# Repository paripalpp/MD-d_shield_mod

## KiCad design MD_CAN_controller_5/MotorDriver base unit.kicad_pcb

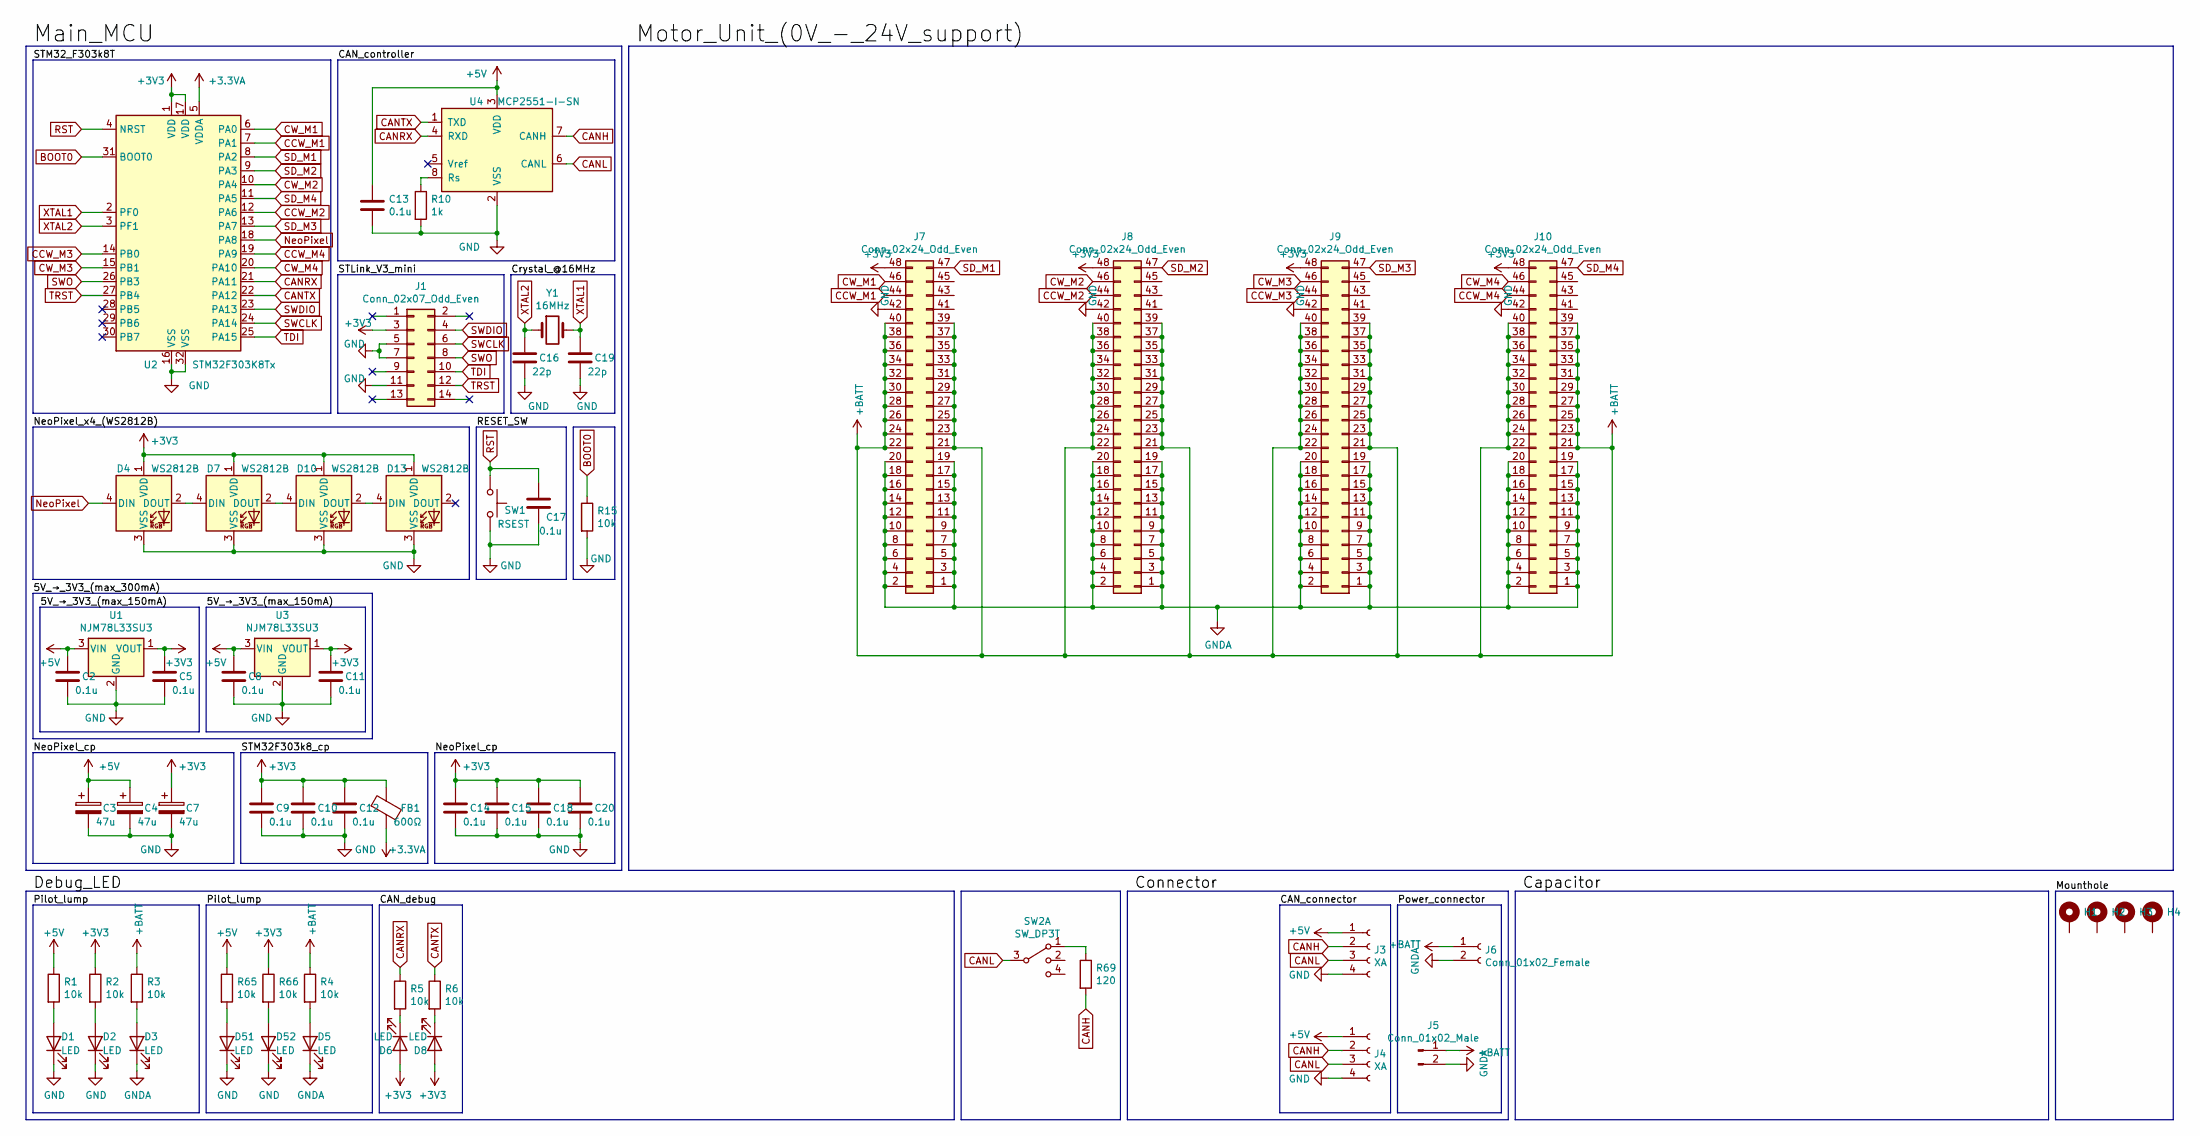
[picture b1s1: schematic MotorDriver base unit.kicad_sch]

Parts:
C2, C5, C8, C9, C10, C11, C12, C13, C14, C15, C17, C18, C20: 0.1u; C_0603_1608Metric
C3, C4, C7: 47u; CP_Elec_6.3x5.2
C16, C19: 22p; C_0603_1608Metric
D1, D2, D3, D5, D6, D8, D51, D52: LED; LED_0603_1608Metric
D4, D7, D10, D13: WS2812B; LED_WS2812B_PLCC4_5.0x5.0mm_P3.2mm
FB1: 600Ω; L_0603_1608Metric
H1, H2, H3, H4: MountingHole_Pad; MountingHole_3.2mm_M3_Pad_Via
J1: Conn_02x07_Odd_Even; PinHeader_2x07_P1.27mm_Vertical
J3, J4: XA; S04B-XASK-1
J5: Conn_01x02_Male; T_connecter_male_horizontal
J6: Conn_01x02_Female; T_connecter_female_horizontal
J7, J8, J9, J10: Conn_02x24_Odd_Even; PinSocket_2x24_P2.54mm_Vertical
R1, R2, R3, R4, R5, R6, R15, R65, R66: 10k; R_0603_1608Metric
R10: 1k; R_0603_1608Metric
R69: 120; R_0603_1608Metric
SW1: RSEST; SW_PUSH_6mm_H4.3mm
SW2: SW_DP3T; CL-SB-13A-01
U1, U3: NJM78L33SU3; SOT-89-3
U2: STM32F303K8Tx; LQFP-32_7x7mm_P0.8mm
U4: MCP2551-I-SN; SOIC-8_3.9x4.9mm_P1.27mm
Y1: 16MHz; Crystal_SMD_HC49-SD

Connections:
+3.3VA: FB1.2, U2.5 (VDDA)
+3V3: C5.1, C7.1, C9.1, C10.1, C11.1, C12.1, C14.1, C15.1, C18.1, C20.1, D4.1 (VDD), D6.2 (A), D7.1 (VDD), D8.2 (A), D10.1 (VDD), D13.1 (VDD), FB1.1, J1.3, J7.48, J8.48, J9.48, J10.48, R2.1, R66.1, U1.1 (VOUT), U2.1 (VDD), U2.17 (VDD), U3.1 (VOUT)
+5V: C2.1, C3.1, C4.1, C8.1, C13.1, J3.1, J4.1, R1.1, R65.1, U1.3 (VIN), U3.3 (VIN), U4.3 (VDD)
+BATT: J5.1, J6.1, J7.21, J7.22, J7.23, J7.24, J7.25, J7.26, J7.27, J7.28, J7.29, J7.30, J7.31, J7.32, J7.33, J7.34, J7.35, J7.36, J7.37, J7.38, J7.39, J7.40, J8.21, J8.22, J8.23, J8.24, J8.25, J8.26, J8.27, J8.28, J8.29, J8.30, J8.31, J8.32, J8.33, J8.34, J8.35, J8.36, J8.37, J8.38, J8.39, J8.40, J9.21, J9.22, J9.23, J9.24, J9.25, J9.26, J9.27, J9.28, J9.29, J9.30, J9.31, J9.32, J9.33, J9.34, J9.35, J9.36, J9.37, J9.38, J9.39, J9.40, J10.21, J10.22, J10.23, J10.24, J10.25, J10.26, J10.27, J10.28, J10.29, J10.30, J10.31, J10.32, J10.33, J10.34, J10.35, J10.36, J10.37, J10.38, J10.39, J10.40, R3.1, R4.1
BOOT0: R15.1, U2.31 (BOOT0)
CANH: J3.2, J4.2, R69.2, U4.7 (CANH)
CANL: J3.3, J4.3, SW2.3, U4.6 (CANL)
CANRX: R5.1, U2.21 (PA11), U4.4 (RXD)
CANTX: R6.1, U2.22 (PA12), U4.1 (TXD)
CCW_M1: J7.44, U2.7 (PA1)
CCW_M2: J8.44, U2.12 (PA6)
CCW_M3: J9.44, U2.14 (PB0)
CCW_M4: J10.44, U2.19 (PA9)
CW_M1: J7.46, U2.6 (PA0)
CW_M2: J8.46, U2.10 (PA4)
CW_M3: J9.46, U2.15 (PB1)
CW_M4: J10.46, U2.20 (PA10)
GND: C2.2, C3.2, C4.2, C5.2, C7.2, C8.2, C9.2, C10.2, C11.2, C12.2, C13.2, C14.2, C15.2, C16.2, C17.2, C18.2, C19.2, C20.2, D1.1 (K), D2.1 (K), D4.3 (VSS), D7.3 (VSS), D10.3 (VSS), D13.3 (VSS), D51.1 (K), D52.1 (K), J1.5, J1.7, J1.11, J3.4, J4.4, J7.42, J8.42, J9.42, J10.42, R10.2, R15.2, SW1.2, U1.2 (GND), U2.16 (VSS), U2.32 (VSS), U3.2 (GND), U4.2 (VSS)
GNDA: D3.1 (K), D5.1 (K), J5.2, J6.2, J7.1, J7.2, J7.3, J7.4, J7.5, J7.6, J7.7, J7.8, J7.9, J7.10, J7.11, J7.12, J7.13, J7.14, J7.15, J7.16, J7.17, J7.18, J7.19, J7.20, J8.1, J8.2, J8.3, J8.4, J8.5, J8.6, J8.7, J8.8, J8.9, J8.10, J8.11, J8.12, J8.13, J8.14, J8.15, J8.16, J8.17, J8.18, J8.19, J8.20, J9.1, J9.2, J9.3, J9.4, J9.5, J9.6, J9.7, J9.8, J9.9, J9.10, J9.11, J9.12, J9.13, J9.14, J9.15, J9.16, J9.17, J9.18, J9.19, J9.20, J10.1, J10.2, J10.3, J10.4, J10.5, J10.6, J10.7, J10.8, J10.9, J10.10, J10.11, J10.12, J10.13, J10.14, J10.15, J10.16, J10.17, J10.18, J10.19, J10.20
NeoPixel: D4.4 (DIN), U2.18 (PA8)
unnamed: D1.2 (A), R1.2
unnamed: D2.2 (A), R2.2
unnamed: D3.2 (A), R3.2
unnamed: D4.2 (DOUT), D7.4 (DIN)
unnamed: D5.2 (A), R4.2
unnamed: D6.1 (K), R5.2
unnamed: D8.1 (K), R6.2
unnamed: D10.2 (DOUT), D13.4 (DIN)
unnamed: D7.2 (DOUT), D10.4 (DIN)
unnamed: D51.2 (A), R65.2
unnamed: D52.2 (A), R66.2
unnamed: R10.1, U4.8 (Rs)
unnamed: R69.1, SW2.1
RST: C17.1, SW1.1, U2.4 (NRST)
SD_M1: J7.47, U2.8 (PA2)
SD_M2: J8.47, U2.9 (PA3)
SD_M3: J9.47, U2.13 (PA7)
SD_M4: J10.47, U2.11 (PA5)
SWCLK: J1.6, U2.24 (PA14)
SWDIO: J1.4, U2.23 (PA13)
SWO: J1.8, U2.26 (PB3)
TDI: J1.10, U2.25 (PA15)
TRST: J1.12, U2.27 (PB4)
XTAL1: C19.1, U2.2 (PF0), Y1.2
XTAL2: C16.1, U2.3 (PF1), Y1.1

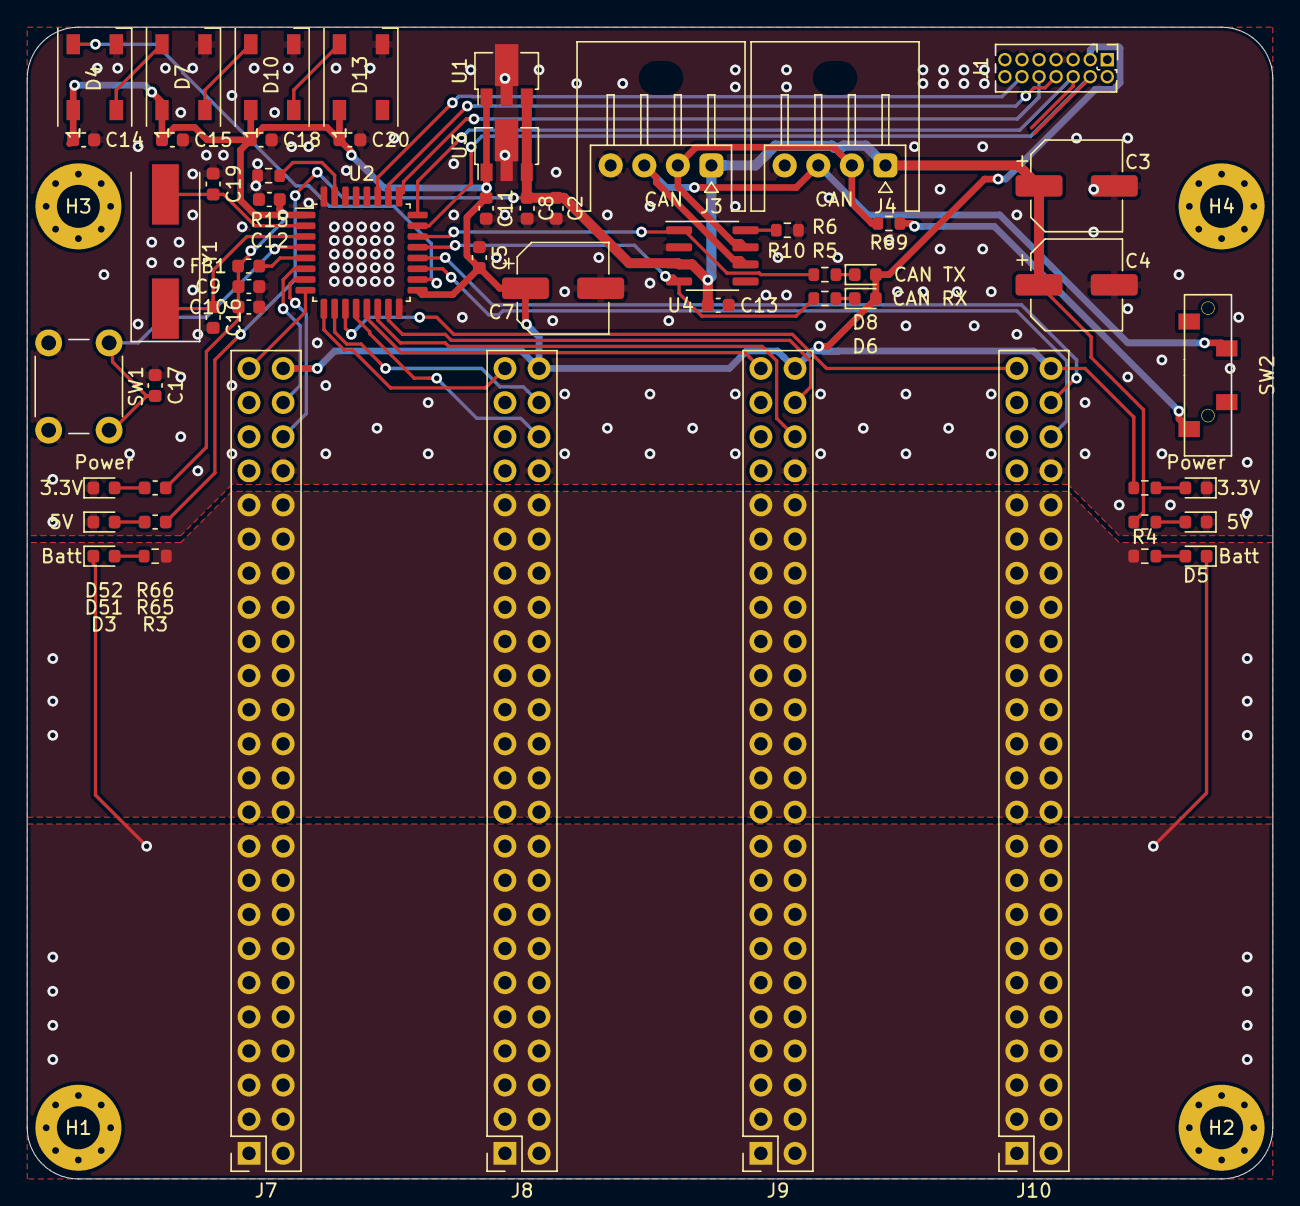
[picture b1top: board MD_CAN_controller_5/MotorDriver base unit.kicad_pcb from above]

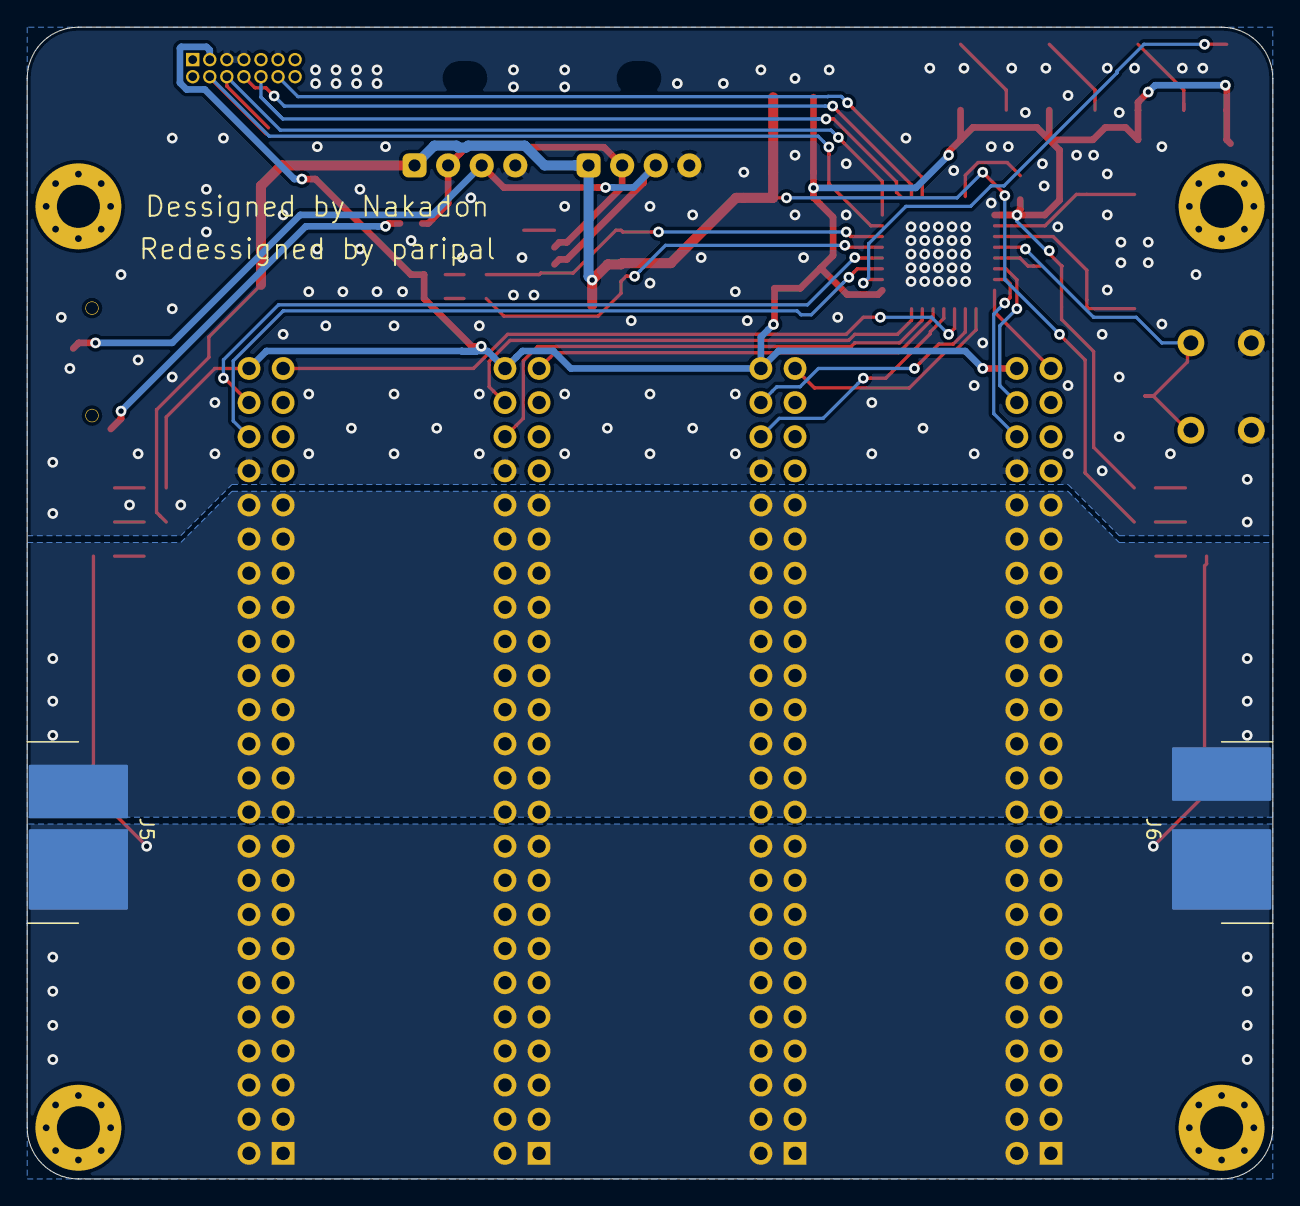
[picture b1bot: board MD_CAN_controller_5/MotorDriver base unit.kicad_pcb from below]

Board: 2 copper layers, 92.7 x 85.7 mm, 62 parts (2 on the bottom side), 45 nets.

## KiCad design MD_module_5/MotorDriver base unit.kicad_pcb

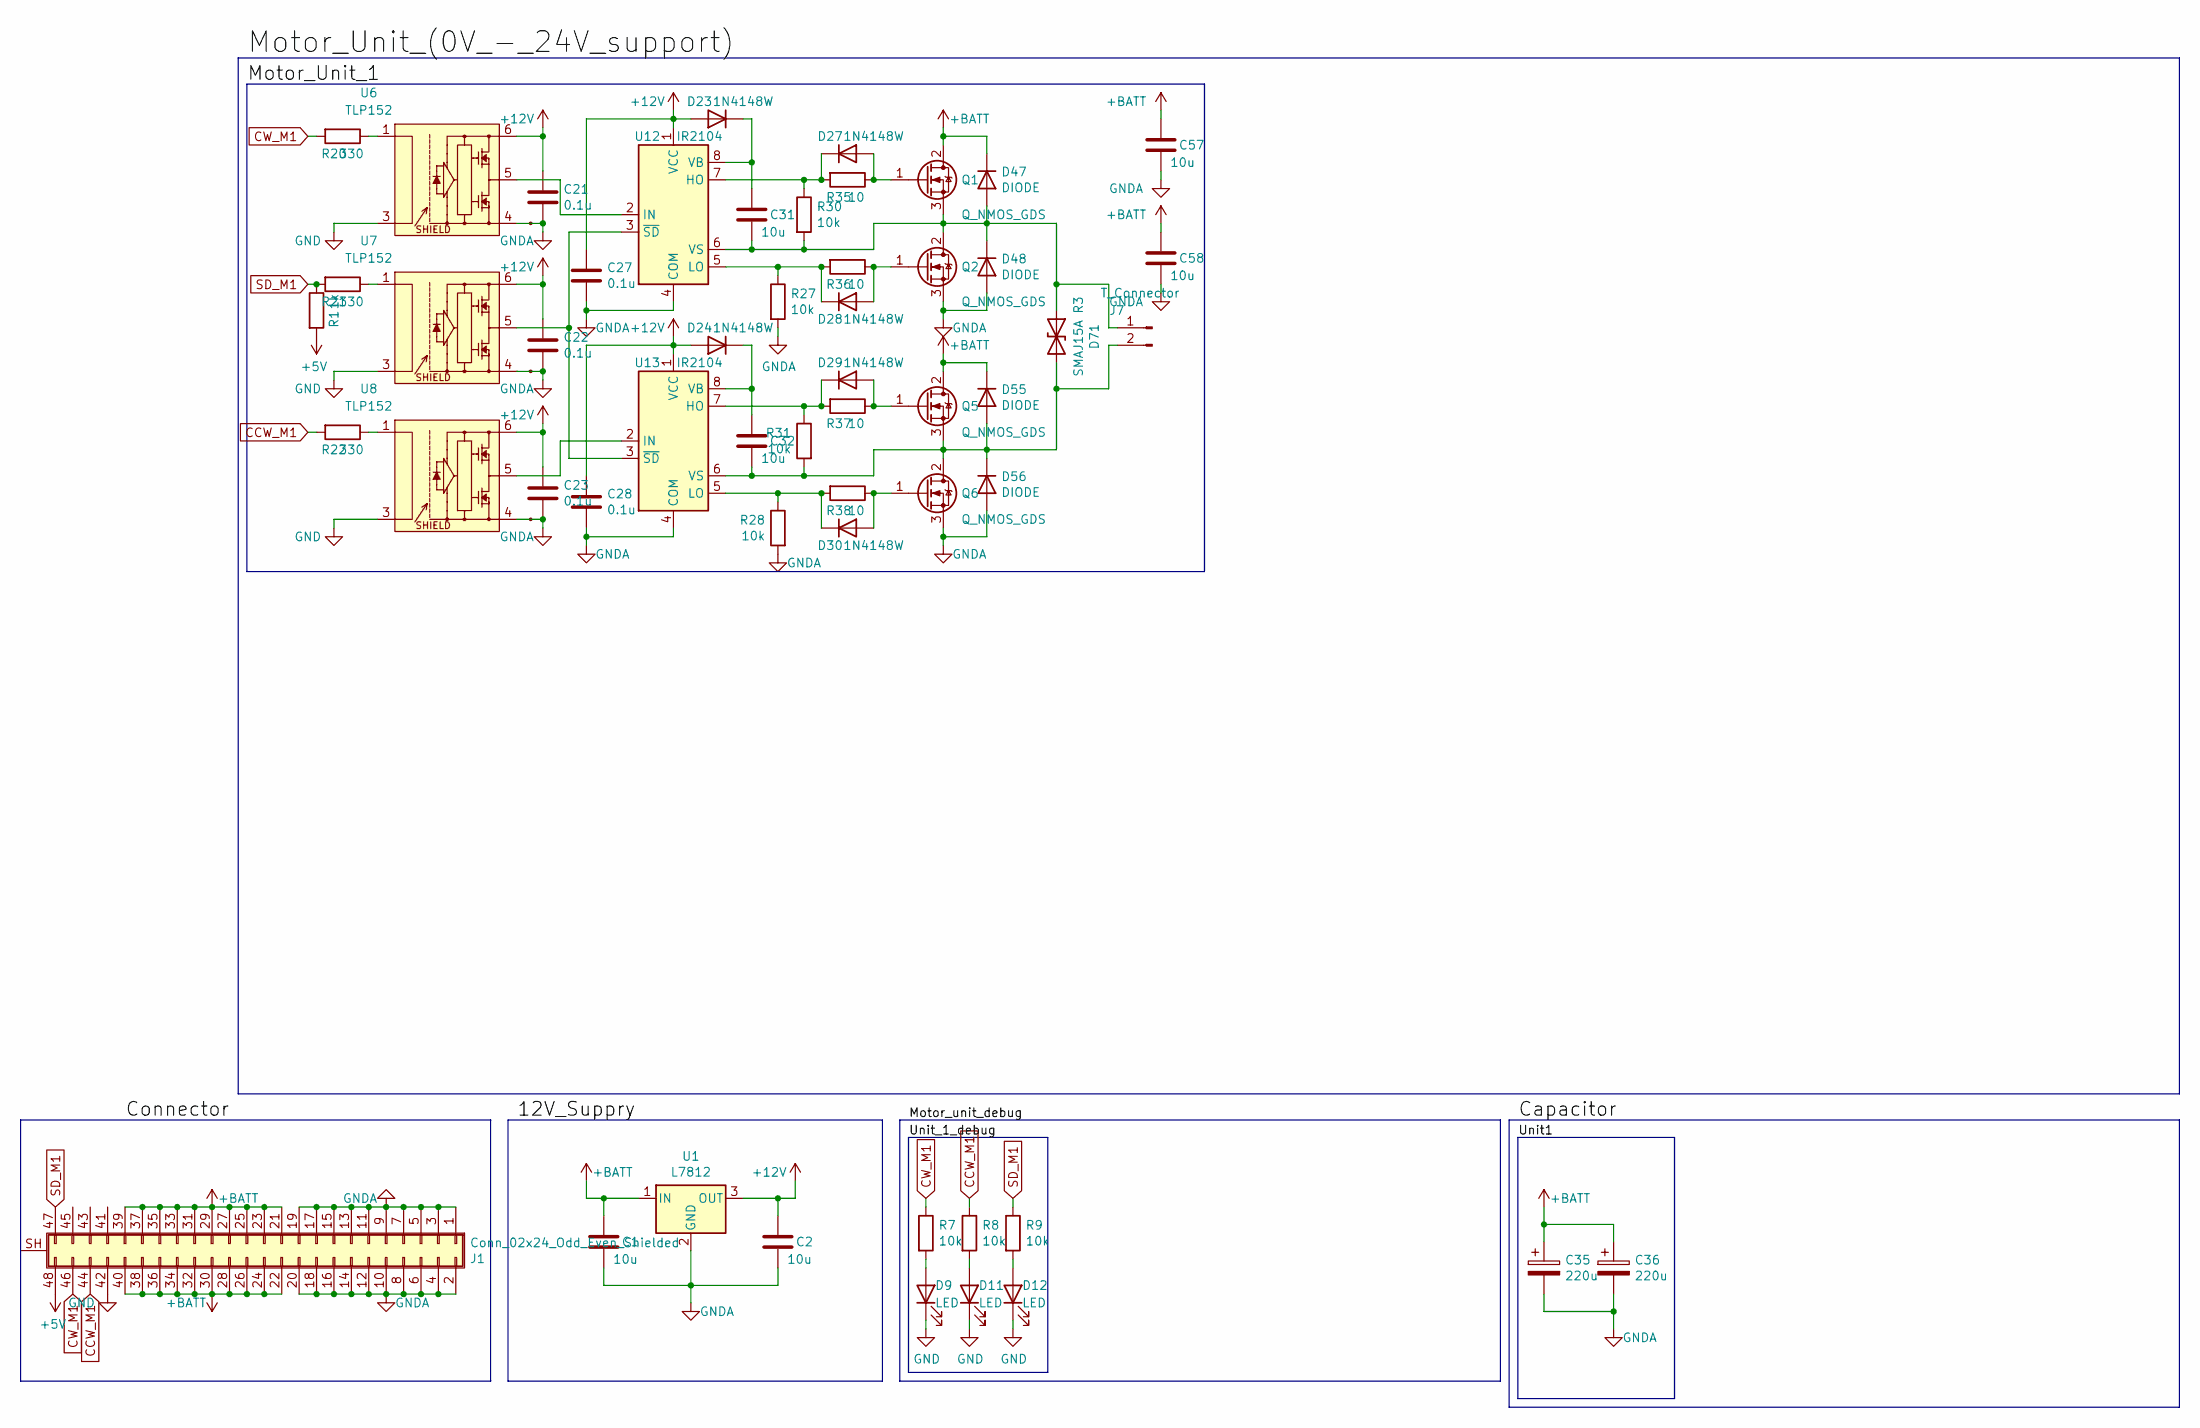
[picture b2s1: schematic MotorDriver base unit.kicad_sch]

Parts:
C1, C57, C58: 10u; C_1210_3225Metric
C2, C31, C32: 10u; C_0805_2012Metric
C21, C22, C23, C27, C28: 0.1u; C_0603_1608Metric
C35, C36: 220u; CP_Elec_10x10
D9, D11, D12: LED; LED_0603_1608Metric
D23, D24, D27, D28, D29, D30: 1N4148W; D_SOD-123F
D47, D48, D55, D56: DIODE; D_MELF_Handsoldering
D71: SMAJ15A R3; D_SMA
J1: Conn_02x24_Odd_Even_Shielded; PinHeader_2x24_P2.54mm_Horizontal
J7: T_Connector; T_connecter_female_horizontal
Q1, Q2, Q5, Q6: Q_NMOS_GDS; TO-263-2
R1: 1k; R_0603_1608Metric
R7, R8, R9, R27, R28, R30, R31: 10k; R_0603_1608Metric
R20, R21, R22: 330; R_0603_1608Metric
R35, R36, R37, R38: 10; R_0603_1608Metric
U1: L7812; TO-252-2
U6, U7, U8: TLP152; SO-6_4.4x3.6mm_P1.27mm
U12, U13: IR2104; SOIC-8_3.9x4.9mm_P1.27mm

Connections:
+5V: J1.48, R1.2
+12V: C2.1, C21.1, C22.1, C23.1, C27.1, C28.1, D23.1 (A), D24.1 (A), U1.3 (OUT), U6.6, U7.6, U8.6, U12.1 (VCC), U13.1 (VCC)
+BATT: C1.1, C35.1, C36.1, C57.1, C58.1, D47.2 (K), D55.2 (K), J1.21, J1.22, J1.23, J1.24, J1.25, J1.26, J1.27, J1.28, J1.29, J1.30, J1.31, J1.32, J1.33, J1.34, J1.35, J1.36, J1.37, J1.38, J1.39, J1.40, Q1.2 (D), Q5.2 (D), U1.1 (IN)
CCW_M1: J1.44, R8.1, R22.2
CW_M1: J1.46, R7.1, R20.2
GND: D9.1 (K), D11.1 (K), D12.1 (K), J1.42, U6.3, U7.3, U8.3
GNDA: C1.2, C2.2, C21.2, C22.2, C23.2, C27.2, C28.2, C35.2, C36.2, C57.2, C58.2, D48.1 (A), D56.1 (A), J1.1, J1.2, J1.3, J1.4, J1.5, J1.6, J1.7, J1.8, J1.9, J1.10, J1.11, J1.12, J1.13, J1.14, J1.15, J1.16, J1.17, J1.18, J1.19, J1.20, Q2.3 (S), Q6.3 (S), R27.2, R28.2, U1.2 (GND), U6.4, U7.4, U8.4, U12.4 (COM), U13.4 (COM)
unnamed: C31.1, D23.2 (K), U12.8 (VB)
unnamed: C31.2, D47.1 (A), D48.2 (K), D71.1 (A1), J7.1, Q1.3 (S), Q2.2 (D), R30.2, U12.6 (VS)
unnamed: C32.1, D24.2 (K), U13.8 (VB)
unnamed: C32.2, D55.1 (A), D56.2 (K), D71.2 (A2), J7.2, Q5.3 (S), Q6.2 (D), R31.2, U13.6 (VS)
unnamed: D9.2 (A), R7.2
unnamed: D11.2 (A), R8.2
unnamed: D12.2 (A), R9.2
unnamed: D27.1 (A), Q1.1 (G), R35.1
unnamed: D27.2 (K), R30.1, R35.2, U12.7 (HO)
unnamed: D28.1 (A), Q2.1 (G), R36.1
unnamed: D28.2 (K), R27.1, R36.2, U12.5 (LO)
unnamed: D29.1 (A), Q5.1 (G), R37.1
unnamed: D29.2 (K), R31.1, R37.2, U13.7 (HO)
unnamed: D30.1 (A), Q6.1 (G), R38.1
unnamed: D30.2 (K), R28.1, R38.2, U13.5 (LO)
unnamed: R20.1, U6.1
unnamed: R21.1, U7.1
unnamed: R22.1, U8.1
unnamed: U6.5, U12.2 (IN)
unnamed: U7.5, U12.3 (~SD), U13.3 (~SD)
unnamed: U8.5, U13.2 (IN)
SD_M1: J1.47, R1.1, R9.1, R21.2

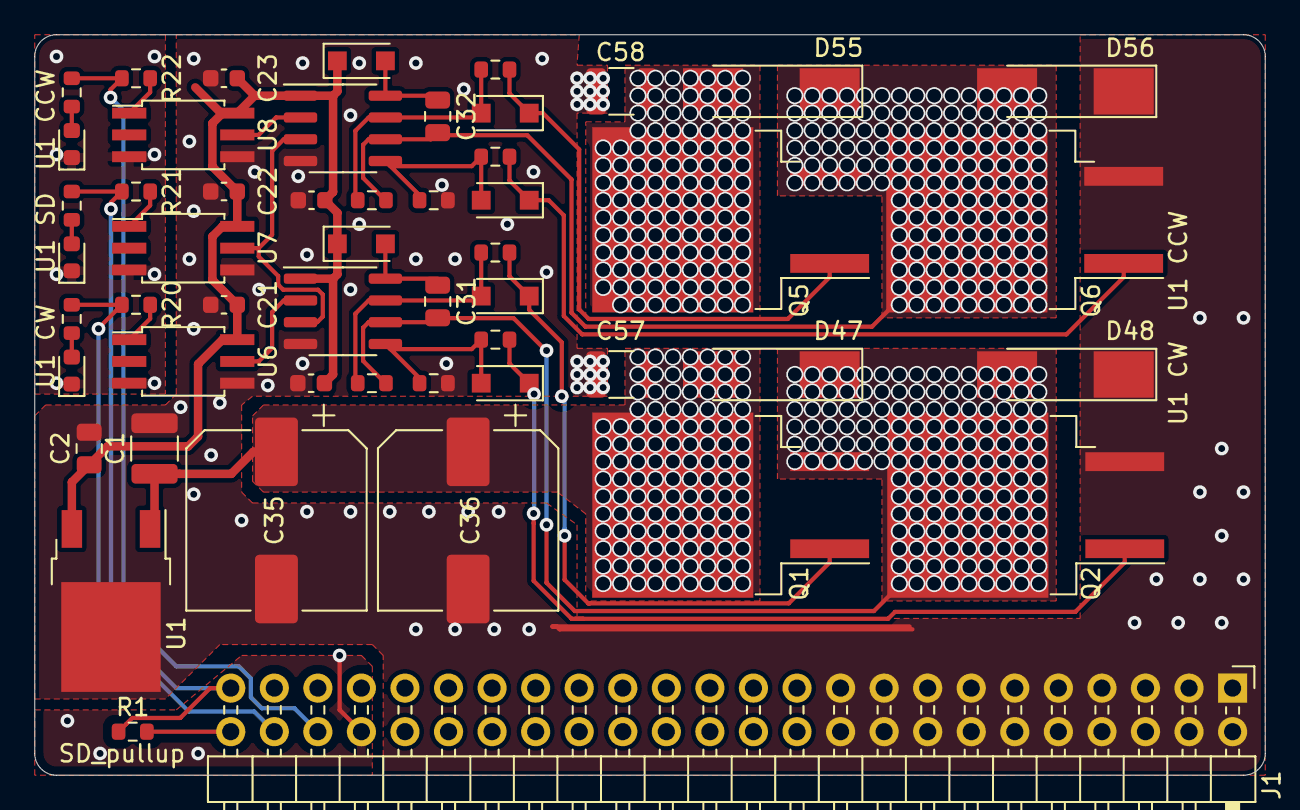
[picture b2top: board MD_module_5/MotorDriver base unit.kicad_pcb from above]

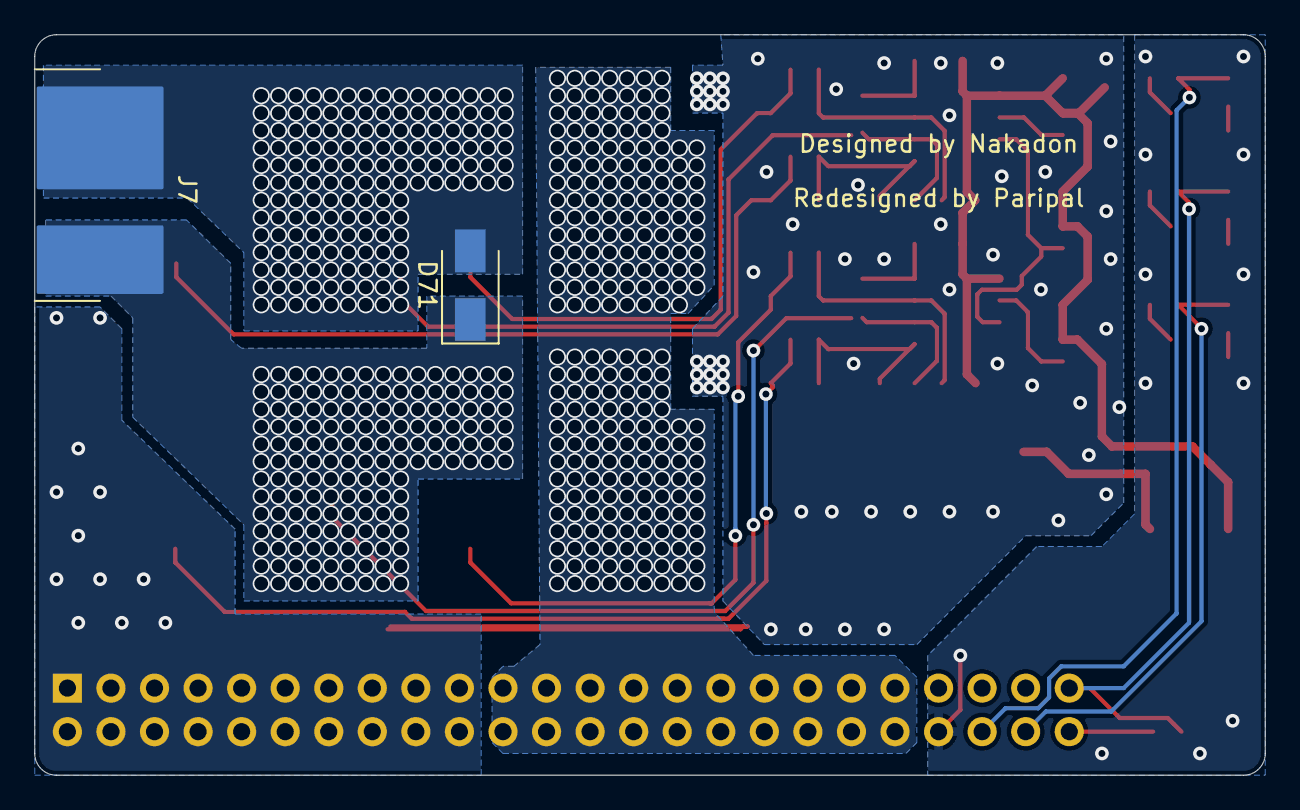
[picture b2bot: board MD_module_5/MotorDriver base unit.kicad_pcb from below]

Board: 2 copper layers, 71.8 x 43.2 mm, 54 parts (2 on the bottom side), 29 nets.
